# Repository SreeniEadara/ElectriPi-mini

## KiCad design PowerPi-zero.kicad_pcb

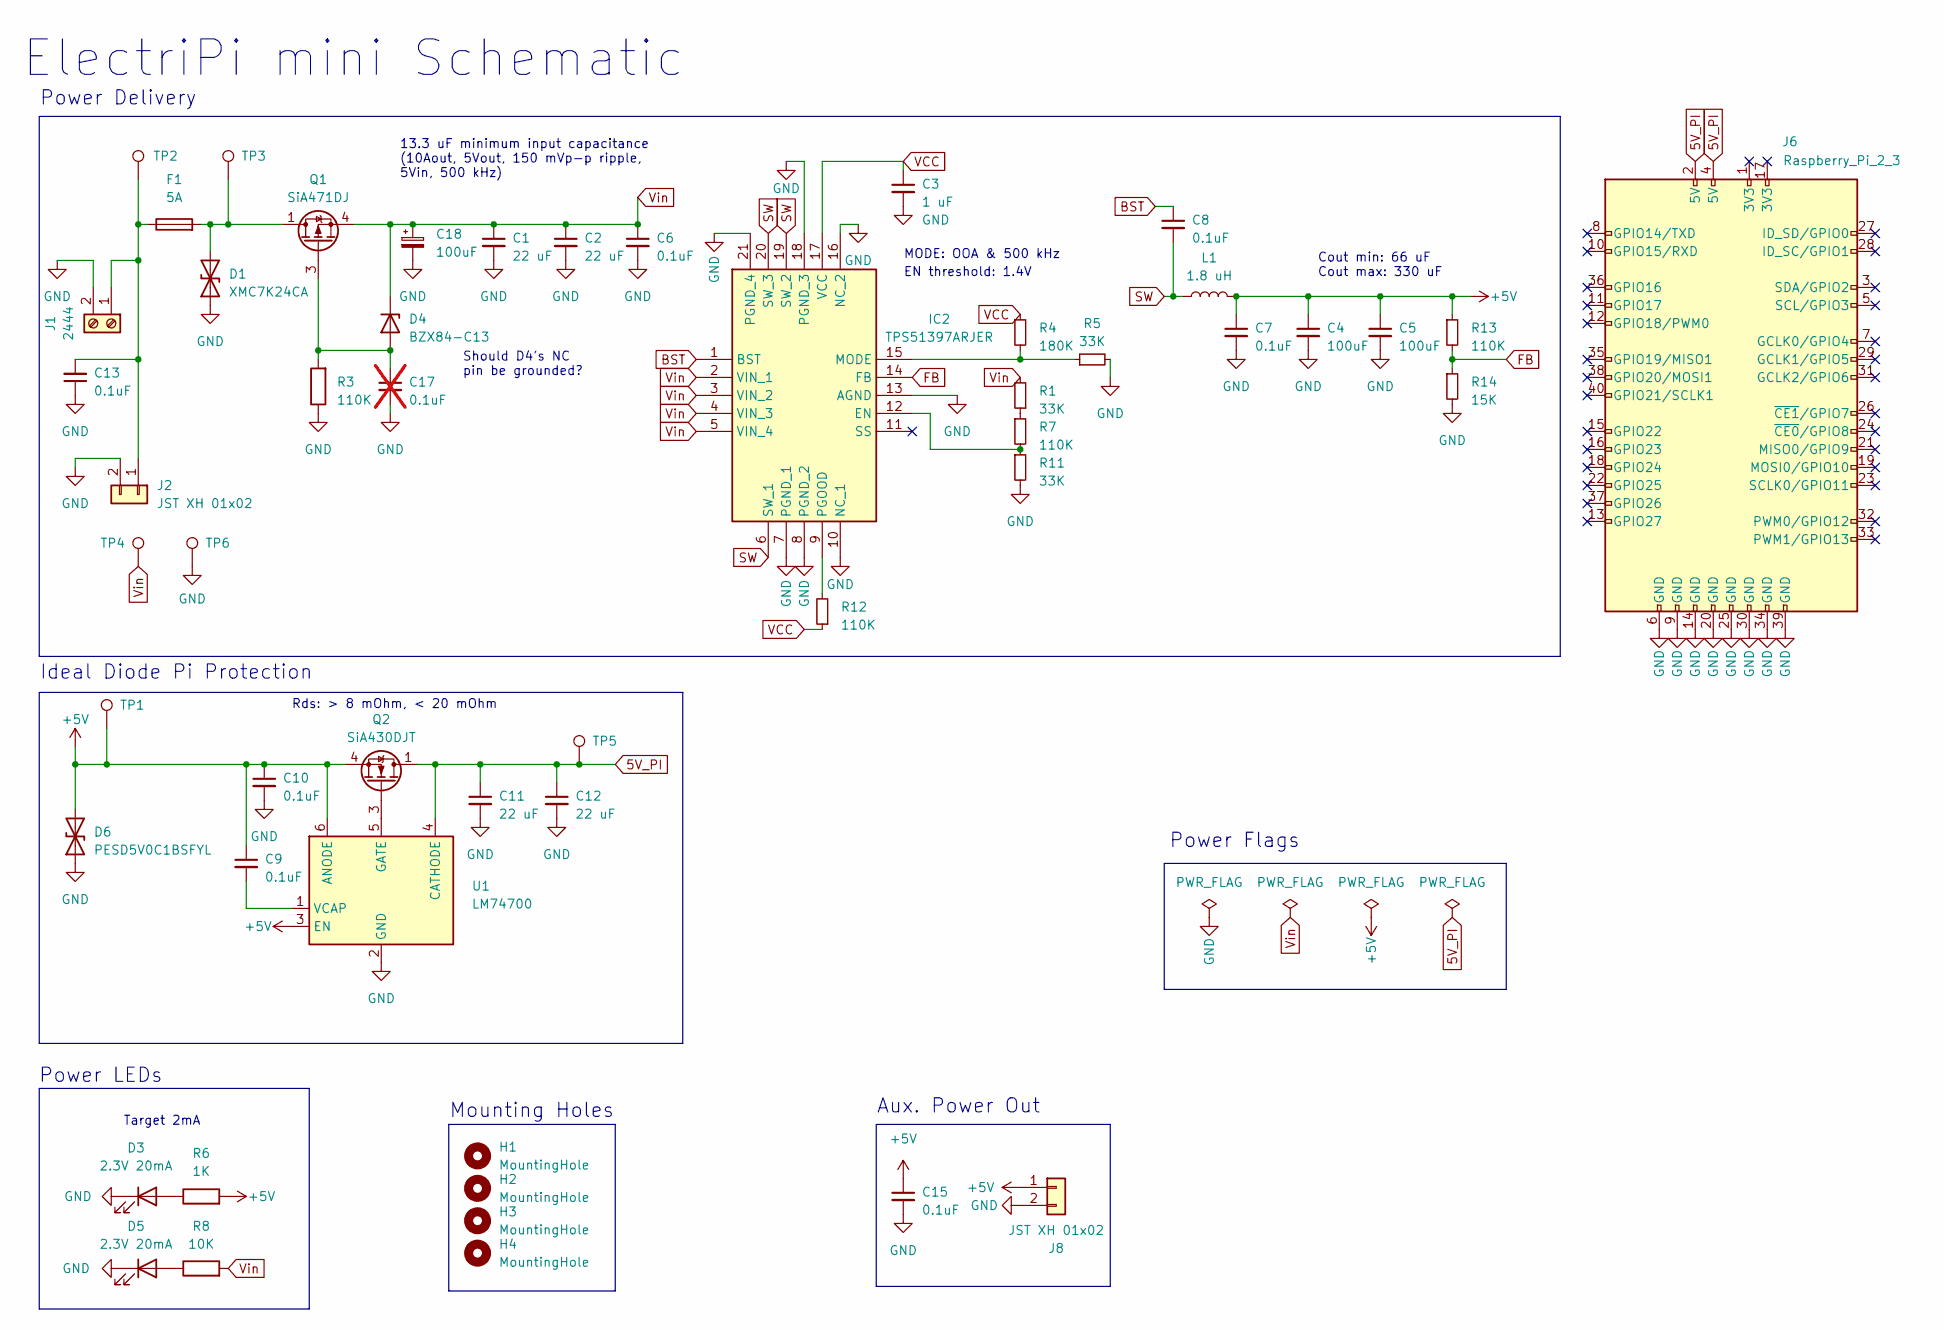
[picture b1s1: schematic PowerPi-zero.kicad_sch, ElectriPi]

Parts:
C1, C2, C11, C12: 22 uF; C_0805_2012Metric; Mouser 810-C2012X5R1V226MAC
C3: 1 uF; C_0603_1608Metric; LCSC C15849
C4, C5: 100uF; C_1206_3216Metric; Mouser 81-GRM31CR61A107MA8L
C6, C7, C8, C9, C10, C13, C15: 0.1uF; C_0402_1005Metric; Mouser 81-GRM155R62A104KE4J
C17: 0.1uF; C_0402_1005Metric; Mouser 81-GRM155R62A104KE4J; not fitted
C18: 100uF; CP_Elec_8x10; Mouser 80-EEV107M050S9MAA
D1: XMC7K24CA; D_SMC; Mouser 78-XMC7K24CAHM3/H
D3, D5: 2.3V 20mA; LED_0603_1608Metric; LCSC C72038
D4: BZX84-C13; SOT-23; Mouser 771-BZX84-C13-T/R
D6: PESD5V0C1BSFYL; Nexperia_DSN0603-2_0.6x0.3mm_P0.4mm; Mouser 771-PESD5V0C1BSFYL
F1: 5A; Fuse_Littelfuse-NANO2-451_453; LCSC C108518
H1, H2, H3, H4: MountingHole; MountingHole_2.7mm_M2.5_DIN965_Pad
IC2: TPS51397ARJER; QFN-20-1EP_3x3mm_P0.45mm_EP1.6x1.6mm_ThermalVias; Manufacturer_Part_Number TPS51397ARJER; Mouser Part Number 595-TPS51397ARJER
J1: 2444; TerminalBlock_4Ucon_1x02_P3.50mm_Horizontal; LCSC C123214
J2, J8: JST XH 01x02; JST_XH_B2B-XH-A_1x02_P2.50mm_Vertical; LCSC C24193
J6: Raspberry_Pi_2_3; PinSocket_2x20_P2.54mm_Vertical
L1: 1.8 uH; L_Vishay_IHLP-4040; LCSC C506636
Q1: SiA471DJ; Vishay_PowerPAK_SC70-6L_Single; Mouser 78-SIA471DJ-T1-GE3
Q2: SiA430DJT; Vishay_PowerPAK_SC70-6L_Single; Mouser 78-SIA430DJT-T1-GE3
R1, R5, R11: 33K; R_0402_1005Metric; LCSC C323721
R3, R7, R12, R13: 110K; R_0402_1005Metric; LCSC C413107
R4: 180K; R_0402_1005Metric; LCSC C413110
R6: 1K; R_0402_1005Metric; LCSC C409028
R8: 10K; R_0402_1005Metric; LCSC C270371
R14: 15K; R_0402_1005Metric; LCSC C319837
TP1, TP2, TP3, TP4, TP5, TP6: TestPoint; TestPoint_Pad_D1.5mm
U1: LM74700; SOT-23-6; Mouser 595-LM74700QDBVRQ1

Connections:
5V_PI: C11.1, C12.1, J6.2 (5V), J6.4 (5V), Q2.1 (D), TP5.1, U1.4 (CATHODE)
+5V: C4.1, C5.1, C7.1, C9.1, C10.1, C15.1, D6.2 (A2), J8.1, L1.2, Q2.4 (S), R6.2, R13.1, TP1.1, U1.3 (EN), U1.6 (ANODE)
BST: C8.1, IC2.1 (BST)
FB: IC2.14 (FB), R13.2, R14.1
GND: C1.2, C2.2, C3.2, C4.2, C5.2, C6.2, C7.2, C10.2, C11.2, C12.2, C13.1, C15.2, C17.2, C18.2, D1.1 (A1), D3.1 (K), D5.1 (K), D6.1 (A1), IC2.7 (PGND_1), IC2.8 (PGND_2), IC2.10 (NC_1), IC2.13 (AGND), IC2.16 (NC_2), IC2.18 (PGND_3), IC2.21 (PGND_4), J1.2, J2.2, J6.6 (GND), J6.9 (GND), J6.14 (GND), J6.20 (GND), J6.25 (GND), J6.30 (GND), J6.34 (GND), J6.39 (GND), J8.2, R3.1, R5.2, R11.2, R14.2, TP6.1, U1.2 (GND)
unnamed: D1.2 (A2), F1.2, Q1.1 (D), TP3.1
unnamed: D3.2 (A), R6.1
unnamed: C17.1, D4.1 (A), Q1.3 (G), R3.2
unnamed: D5.2 (A), R8.1
unnamed: IC2.12 (EN), R7.2, R11.1
unnamed: IC2.15 (MODE), R4.2, R5.1
unnamed: IC2.9 (PGOOD), R12.2
unnamed: C13.2, F1.1, J1.1, J2.1, TP2.1
unnamed: Q2.3 (G), U1.5 (GATE)
unnamed: R1.1, R7.1
unnamed: C9.2, U1.1 (VCAP)
SW: C8.2, IC2.6 (SW_1), IC2.19 (SW_2), IC2.20 (SW_3), L1.1
VCC: C3.1, IC2.17 (VCC), R4.1, R12.1
Vin: C1.1, C2.1, C6.1, C18.1, D4.3 (K), IC2.2 (VIN_1), IC2.3 (VIN_2), IC2.4 (VIN_3), IC2.5 (VIN_4), Q1.4 (S), R1.2, R8.2, TP4.1

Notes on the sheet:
Ideal Diode Pi Protection
Mounting Holes
Target 2mA
Rds: > 8 mOhm, < 20 mOhm
MODE: OOA & 500 kHz
Cout min: 66 uF Cout max: 330 uF
ElectriPi mini Schematic
13.3 uF minimum input capacitance (10Aout, 5Vout, 150 mVp-p ripple, 5Vin, 500 kHz)
EN threshold: 1.4V
Should D4's NC pin be grounded?
Aux. Power Out
Power Flags
Power LEDs
Power Delivery

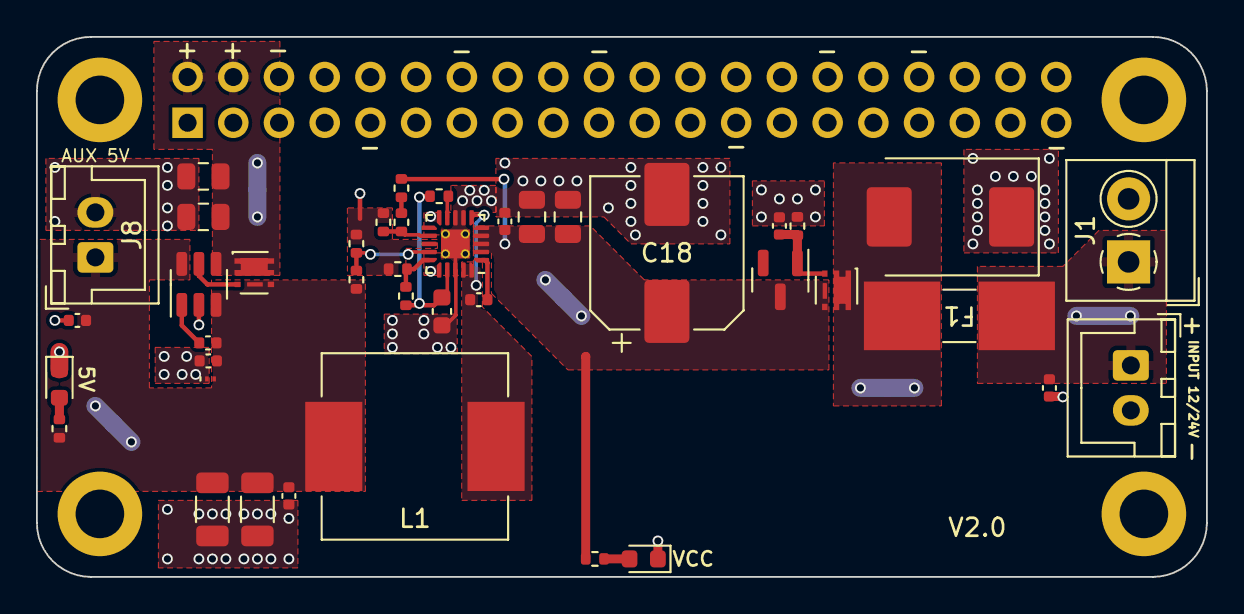
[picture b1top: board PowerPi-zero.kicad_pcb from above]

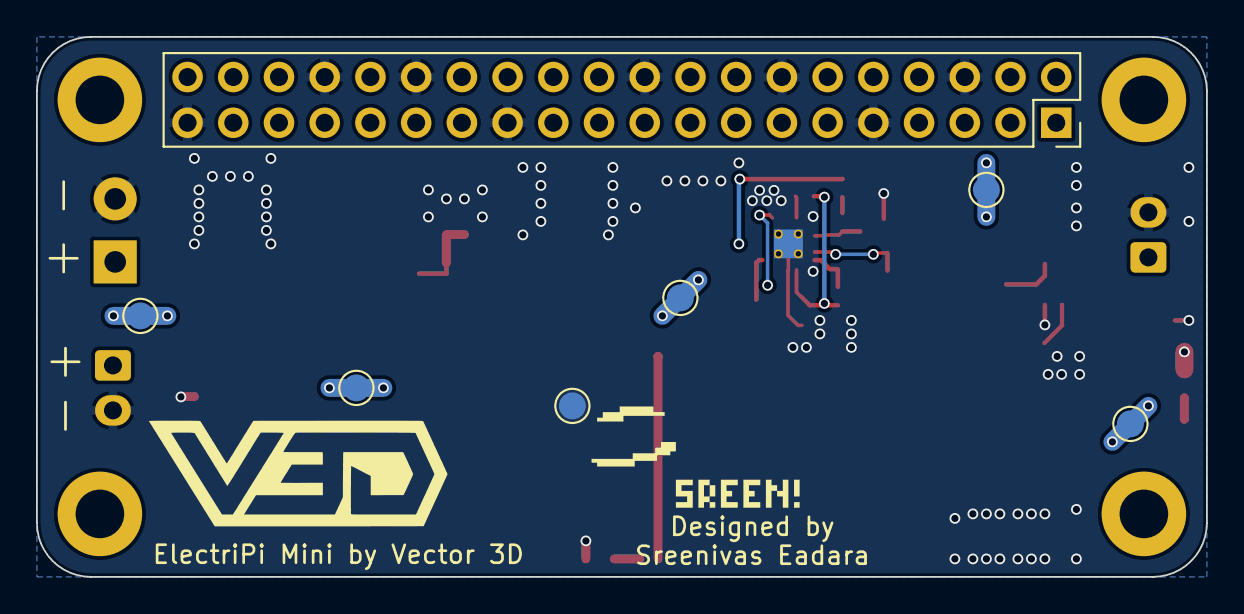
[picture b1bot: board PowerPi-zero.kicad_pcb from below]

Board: 2 copper layers, 65.0 x 30.0 mm, 52 parts (7 on the bottom side), 19 nets.

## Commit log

2022-05-22 renaming to PowerPi-zero
2022-05-22 Layout complete for PowerPi zero
2022-05-22 cleanup
2022-05-25 updated layout
2022-05-26 updated layout and improved copper balance
2022-07-07 update to 1000 uF output electrolytic capacitor
2022-12-19 Brought full design up to date with ElectriPi
    Main development was done on ElectriPi so now ElectriPi mini matches those developments
2022-12-20 Updated layout, esp. component position around input side
2022-12-20 Changed thermal reliefs for ICL
2022-12-20 updated gitignore for meta and zip
2022-12-20 update gitignore
2022-12-20 Final tweaks for producion
2024-01-25 Upgrade to TI part, matching ElectriPi.
2024-01-25 alter component position
2024-01-25 update component position, better layout
2024-01-26 layout drafted, silk issues remain
2024-01-26 silk fixed, DRC and DFM changes
2024-01-26 fix thermal connections for pours
